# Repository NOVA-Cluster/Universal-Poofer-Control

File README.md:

# Universal Poofer Control — revision A.3

Controller platform intended for creating theatrical flame effects devices (poofers), including stage effects, flame-art installations and custom theatrical projects. The current design remains an engineering preview, not a qualified live-effects system.

Editable KiCad 10 design for ESP32-S3-WROOM-1-N8, eight relay-controlled 12 VDC valves and eight **grounded switches, active LOW**, with nominal **20 mA board-sourced wetting current**. The field circuits are designed for continuous ±100 V relative to shared return, including power-off conditions. Physical fault and temperature qualification remains required.

Open `Universal_Poofer_Control.kicad_pro`. The schematic has **24 numbered A3 sheets**, grouped by function with repeated channel layouts and local wiring. The **200 × 160 mm PCB is placement only**: 0.5 mm footprint-origin grid, no tracks, vias or copper pours. `AGENTS.md` makes these engineering and appearance standards persistent.

**New to the board?** Start with the [Hardware User Guide](docs/hardware-user-guide.md), the maintained customer-facing source of truth for features, project ideas, wiring, first-use commissioning, expansion and schematic navigation. A.3 remains an engineering preview until qualification.

## Files

| Deliverable | Location |
|---|---|
| Customer hardware guide | `docs/hardware-user-guide.md` / `output/pdf/Universal_Poofer_Control_Hardware_User_Guide.pdf` |
| Editable schematic / board | `Universal_Poofer_Control.kicad_sch` / `.kicad_pcb` |
| Schematic PDF | `output/pdf/Universal_Poofer_Control_A3.pdf` |
| Board preview | `output/pcb/placement_top.png` / `.pdf` |
| Full hardware review | `docs/hardware-design-review-A3.md` |
| Analog and stop evidence | `docs/hardware-topology-review.md`, `docs/hardware-stop-logic-review.md` |
| Complete connector reference | `docs/connector-pinouts.md` |
| Arduino / PlatformIO project | `firmware/` |
| Exact JLC assembly BOM / stock | `bom/JLCPCB_BOM.csv`, `bom/assembly_availability.csv` |

## Power and valves

J1: pin 1 regulated **5.0–5.25 V, ≥1 A**, pin 2 GND. J2: pin 1 **12 V, ≥0.5 A**, pin 2 GND, powering analog circuits and eight approximately 30 mA relay coils. Both supplies share logic/input GND. Each expansion module has independent supplies; chain headers have no power pins.

Feed each `J31…J38.1 / COM` from an **individually fused external 12 V valve supply**. Connect its valve between `J41…J48.1 / NO` and `.2 / RETURN`, and connect RETURN to that external supply's negative. Valve RETURN is separate from logic GND. The aggregate valve current does not pass through a common board power header. Plan for **1 A per valve**. The relays' 10 A resistive-contact rating is not the header or inductive-load rating. NC is auxiliary and must not be used for shutdown-controlled valve loads.

All interfaces are 2.54 mm / 100 mil headers. Every resistor/capacitor is **0805**. Ordinary ICs are SOIC; other packages are DPAK, SOT-223, SOT-23 and SMA/SMB. The ESP32 is a replaceable castellated module. There are no 0402/0603 passives or TSSOP logic.

## Switch inputs

Close a dry contact between `J11…J18.1 / FIELD` and `.2 / GND`. LOW means closed; an open contact is inactive. A compensated LM2902 / HV PNP source supplies approximately 20 mA to a grounded contact. A backup limiter bounds saturation-recovery surges. Independent protected paths sense contact state and negative faults.

Closed FIELD must be ≤0.3 V including wiring/contact drop; ≤10 Ω total series-loop contact/return resistance (including every contact and cable in an expansion chain) is a conservative system target. Wetting is nominal, not calibrated or a guaranteed 20 mA minimum. Source accuracy, all-channel settling, MLCC capacitance, cold compliance, fault quench and hot powered-off leakage need prototype tests.

Each module captures 16 bits: active-HIGH fault byte, then active-LOW contact byte. Firmware computes `closed = (~contacts_n) & (~faults)`. Fault detection has a finite threshold: small negative voltages near ground can still read as closed. ±100 V endurance does not imply every intermediate voltage has a unique diagnostic interpretation. This protection applies only to FIELD pins; power, GPIO, I²C, expansion logic and GND retain ordinary limits.

## Hardware emergency stop

J9 connects an external **NC contact** between ESTOP_FIELD and ESTOP_CHAIN_OUT. Opening the loop, disconnecting it, or asserting its field fault removes permission. The master supplies nominal 20 mA. Fit **J10 ground termination only on the last module**; on a single board it is that board. Remove intermediate terminators.

Hardware clears an edge-triggered RUN flip-flop, disables actual 595 `/OE`, and cuts relay-coil power. A 3.3 V supervisor blocks startup/brownout; logic-powered supply monitors also clear RUN on loss of 5 V or raw 12 V (nominal trips about 4.27 V / 8.88 V). Restoring the loop or a supply cannot restart while ARM is held. A fresh arm edge is required. Actual hardware inhibit propagates downstream without firmware cooperation.

GPIO18 reads protected loop permission; GPIO21 reads protected local RUN. Series isolation prevents GPIO backdrive from overriding hardware. GPIO2 observes the physical host jumper through 100 kΩ.

This is a single-channel prototype shutdown circuit. Coil removal cannot open a welded relay contact, and a short across an NC contact can bypass that contact. Use an independent valve-power disconnect where those faults must stop flow. Measure actual relay/valve closure time and clamp energy. No safety certification or shutdown-time rating is established.

## Expansion and I²C

Connect J21 DOWN to the next J20 UP with matching pin numbers. Fit **JP1 on exactly one host**, leave it absent on expanders, and configure roles with power off. Reset after role changes. Do not hot-plug an armed control chain.

| Pin | J20 UP | J21 DOWN |
|---:|---|---|
| 1, 2 | GND | GND |
| 3 | Clock input | Buffered clock |
| 4 | 595 serial input | Local 595 QH′ |
| 5 | Input stream returned upstream | Input stream from next module |
| 6 | Latch input | Buffered latch |
| 7 | Active-low arm/inhibit input | Actual hardware-gated inhibit |
| 8 | Clear input | Buffered clear |
| 9 | Parallel-load input | Buffered parallel load |
| 10 | GND | GND |
| 11 | ESTOP_FIELD | ESTOP_CHAIN_OUT |
| 12, 13, 14 | GND | GND |
| **15** | **I²C SDA common bus** | **I²C SDA common bus** |
| **16** | **I²C SCL common bus** | **I²C SCL common bus** |

LVC244 buffers regenerate shift signals with power-off isolation and 33 Ω series resistors. UP controls have their own safe pulls, so an unplugged expander inhibits. The return tail pulls HIGH, filling absent-module fault bytes with FF. Write 595 bytes farthest-first and read 165 words host-first. Firmware supports a configured **1–32 modules**, each adding 8 output and 16 input bits; this allocation is not a qualified cable-length or physical-chain limit.

I²C uses GPIO8/SDA and GPIO9/SCL on each private MCU B-side bus, isolated onto the common A-side by PCA9517A. Only A sides join together. Fit JP2 at one common pullup provider, normally the host: **2.2 kΩ common**, **4.7 kΩ private** pullups. Start at **100 kHz**, qualify common capacitance ≤400 pF and LOW/high/rise-time/leakage behavior. Thirty-two buffers can consume 224 pF before cables. Unique peripheral addresses and bus loading are independent of shift-chain expansion. [NXP PCA9517A datasheet](https://www.nxp.com/docs/en/data-sheet/PCA9517A.pdf); see `docs/i2c-interface-review.md`.

## GPIO, programming and firmware

| Function | GPIO |
|---|---:|
| Clock / output serial / input serial | 6 / 4 / 5 |
| Latch / MCU inhibit / clear / input load | 7 / 15 / 16 / 17 |
| Loop permission / local RUN / role monitor | 18 / 21 / 2 |
| I²C SDA / SCL | 8 / 9 |
| UART TX / RX | 43 / 44 |
| USB D− / D+ | 19 / 20 |

J3/J4 expose module pins 1–40; pad 41 is grounded on the PCB. GPIO0/3/45/46 are straps. J6 is EN/GND/BOOT; J7 is TX/RX/GND for a 3.3 V UART adapter. Exposed USB signals need a suitable protected external connection. Every header pin, including J5 debug/service access, is listed in `docs/connector-pinouts.md`.

The Arduino/PlatformIO scaffold starts inhibited, clears/latches all configured outputs, requires explicit arm and hardware RUN acknowledgement, and supports bounded 1–1000 ms pulses with a 500 ms renewable control lease. I²C scans are explicit and disarmed-only. It does not automatically map switches to valves. Nothing has been flashed.

From `firmware/`: `pio run -e poofer_uart -e poofer_usb -e poofer_chain32_compile`; `pio test -e native`. `firmware/README.md` documents an isolated build environment. Three target builds and all 24 tests passed; physical timing, interrupts and watchdog remain hardware tests.

## Review, assembly and regeneration

The full review records native ERC, exported-netlist contract checks, saved-board parity, placement DRC, schematic/PCB/cross/thermal/EMC/lifecycle analyzers, generic SPICE and dedicated analog/stop models, with evidence and limitations. The unrouted PCB is not a fabrication release; production Gerbers and final routing/CPL validation have not been produced.

`scripts/build_schematic.py` invokes the A.3 builder; `scripts/build_pcb.py` reproduces placement; `scripts/validate_a3.py` checks the authoritative KiCad-exported netlist. Preserve and reconcile manual or unsaved editor work before regeneration. Local KiCad CLI/pcbnew paths must match the installation. Earlier incompatible active-HIGH / wetting-sink revisions are preserved locally under ignored `archive/`; they are not part of a fresh clone. See [repository contents](docs/repository-content.md) for the versioned sources and local artifacts.

All exact parts had JLC assembly inventory on 2026-10-03; Basic was preferred, with Extended devices retained where electrical/package requirements justify them. Mixed SMT/THT header/relay assembly needs the appropriate service and quote. Recheck stock and orientations at ordering. [JLC assembly capabilities](https://jlcpcb.com/capabilities/pcb-assembly-capabilities). Inventory is not lifecycle evidence: the available LCSC audit returns unknown lifecycle status; production release still needs manufacturer/distributor lifecycle checks.

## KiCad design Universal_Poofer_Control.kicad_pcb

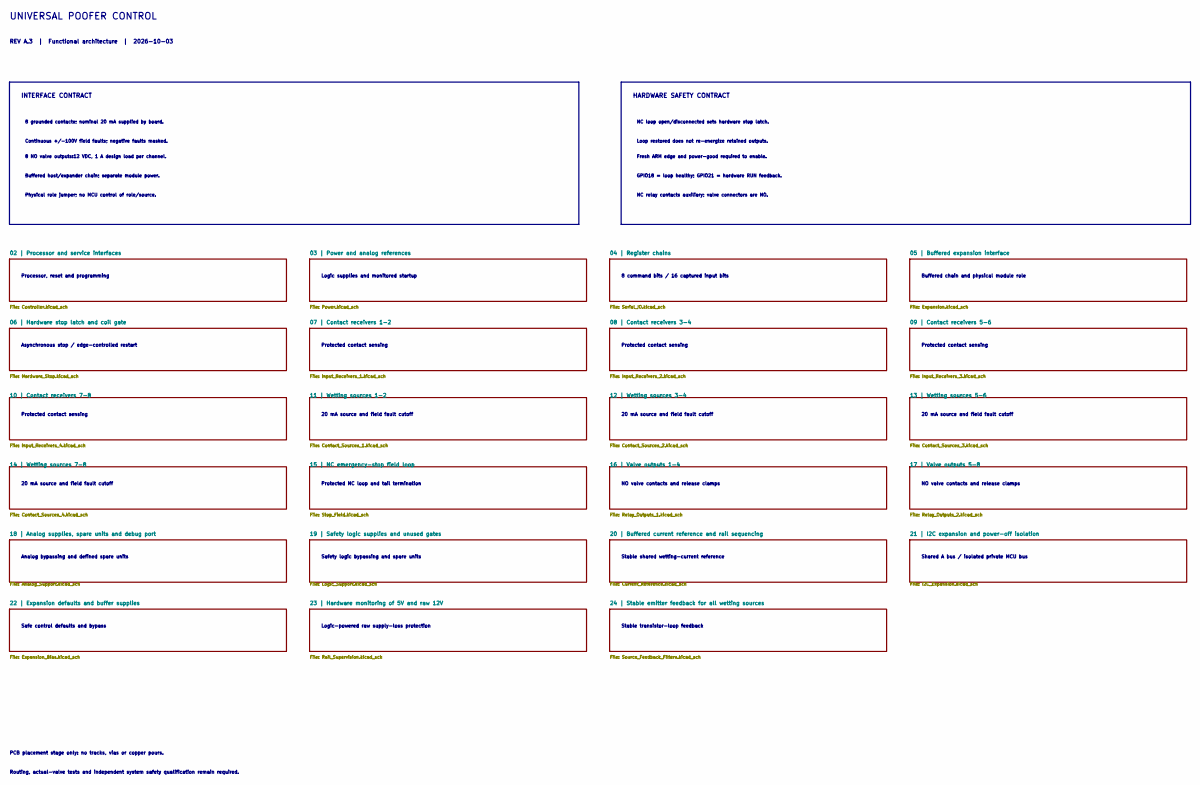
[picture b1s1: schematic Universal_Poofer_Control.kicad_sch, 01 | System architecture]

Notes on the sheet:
UNIVERSAL POOFER CONTROL
REV A.3 | Functional architecture | 2026-10-03
INTERFACE CONTRACT
HARDWARE SAFETY CONTRACT
8 grounded contacts; nominal 20 mA supplied by board.
Continuous +/-100V field faults; negative faults masked.
8 NO valve outputs:12 VDC, 1 A design load per channel.
Buffered host/expander chain; separate module power.
Physical role jumper; no MCU control of role/source.
NC loop open/disconnected sets hardware stop latch.
Loop restored does not re-energize retained outputs.
Fresh ARM edge and power-good required to enable.
GPIO18 = loop healthy; GPIO21 = hardware RUN feedback.
NC relay contacts auxiliary; valve connectors are NO.
Processor, reset and programming
Logic supplies and monitored startup
8 command bits / 16 captured input bits
Buffered chain and physical module role
Asynchronous stop / edge-controlled restart
Protected contact sensing
20 mA source and field fault cutoff
Protected NC loop and tail termination
NO valve contacts and release clamps
Analog bypassing and defined spare units
Safety logic bypassing and spare units
Stable shared wetting-current reference
Shared A bus / isolated private MCU bus
Safe control defaults and bypass
Logic-powered raw supply-loss protection
Stable transistor-loop feedback
PCB placement stage only: no tracks, vias or copper pours.
Routing, actual-valve tests and independent system safety qualification remain required.

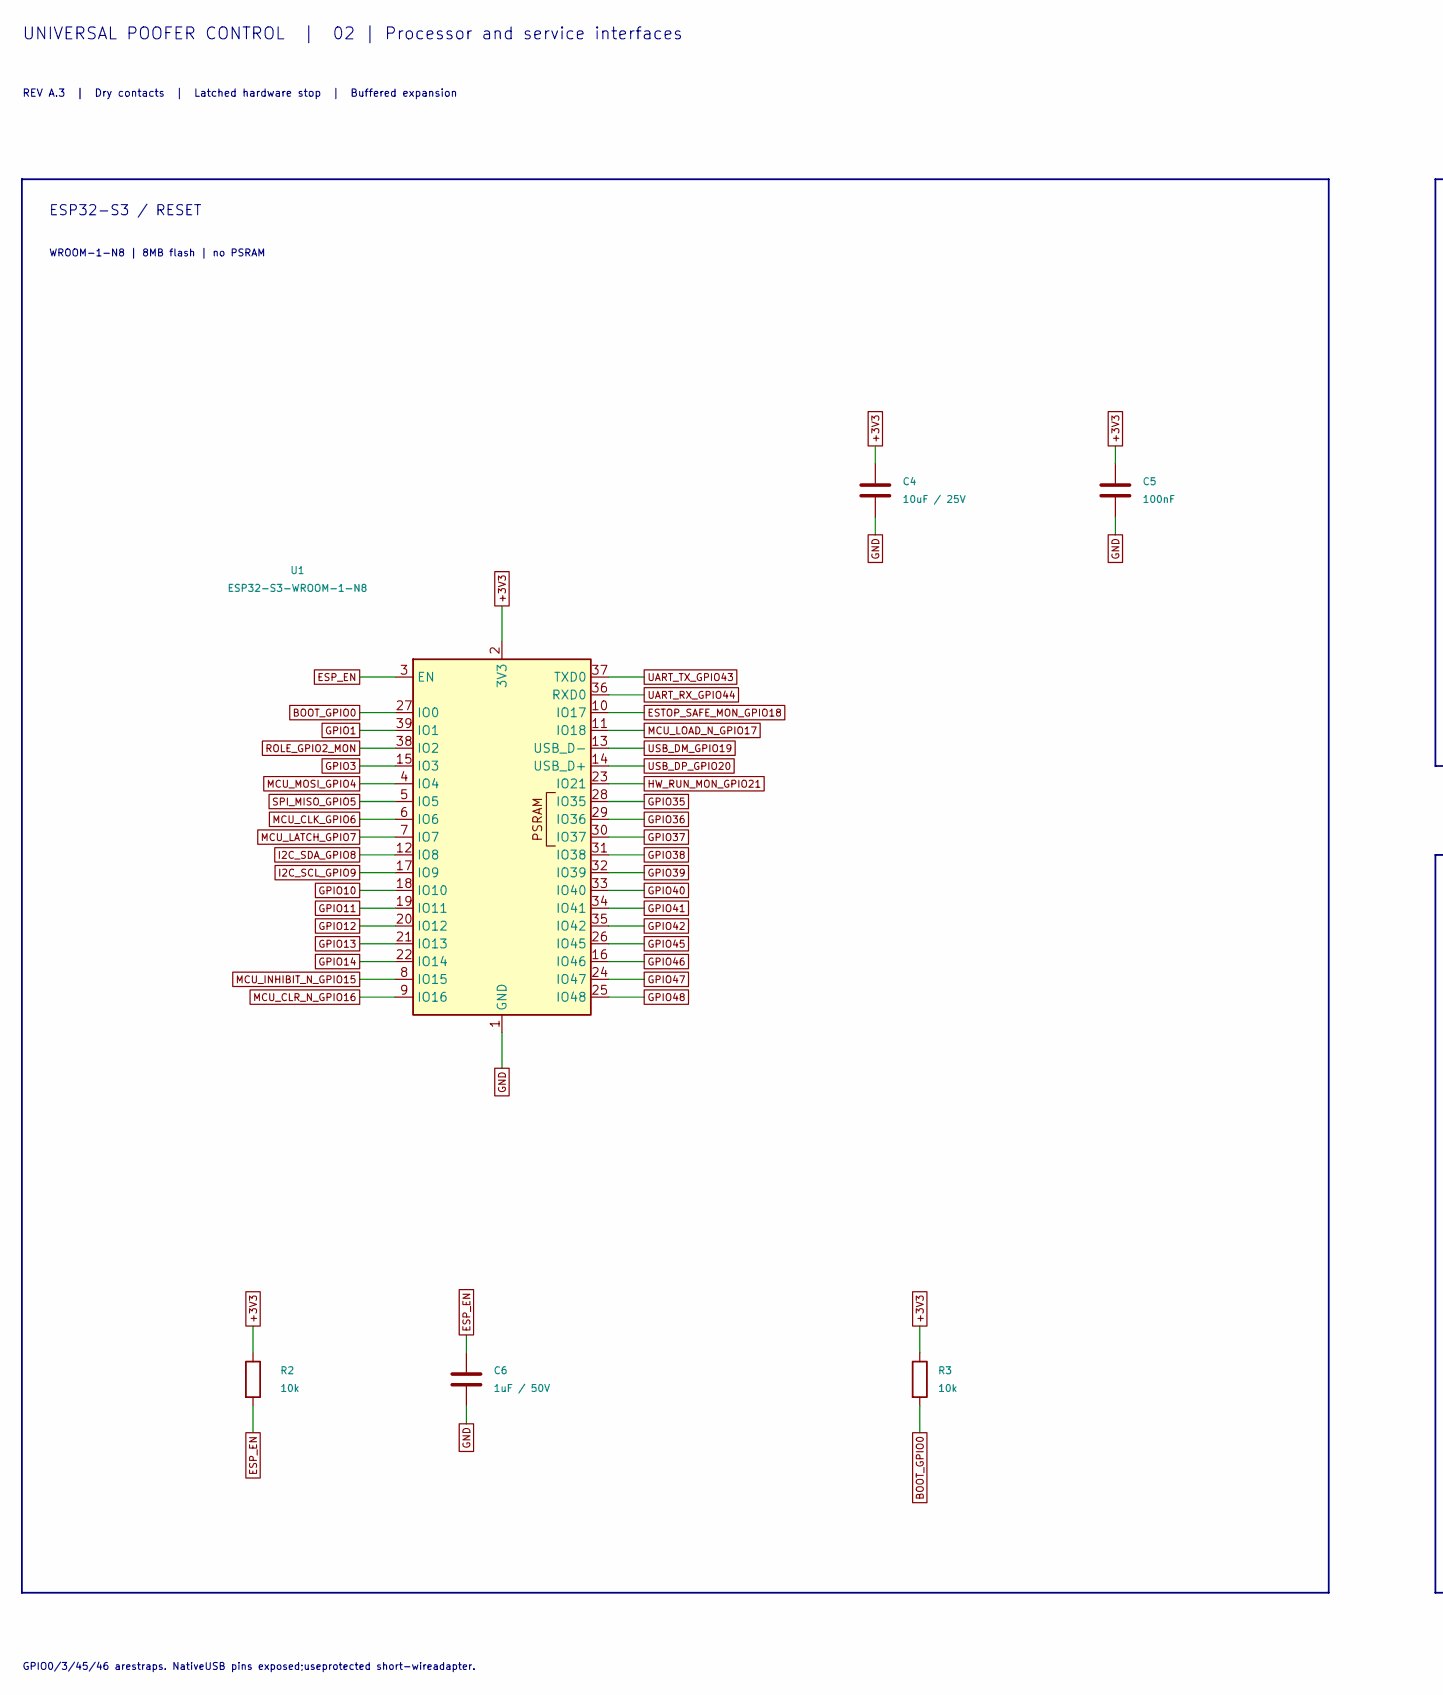
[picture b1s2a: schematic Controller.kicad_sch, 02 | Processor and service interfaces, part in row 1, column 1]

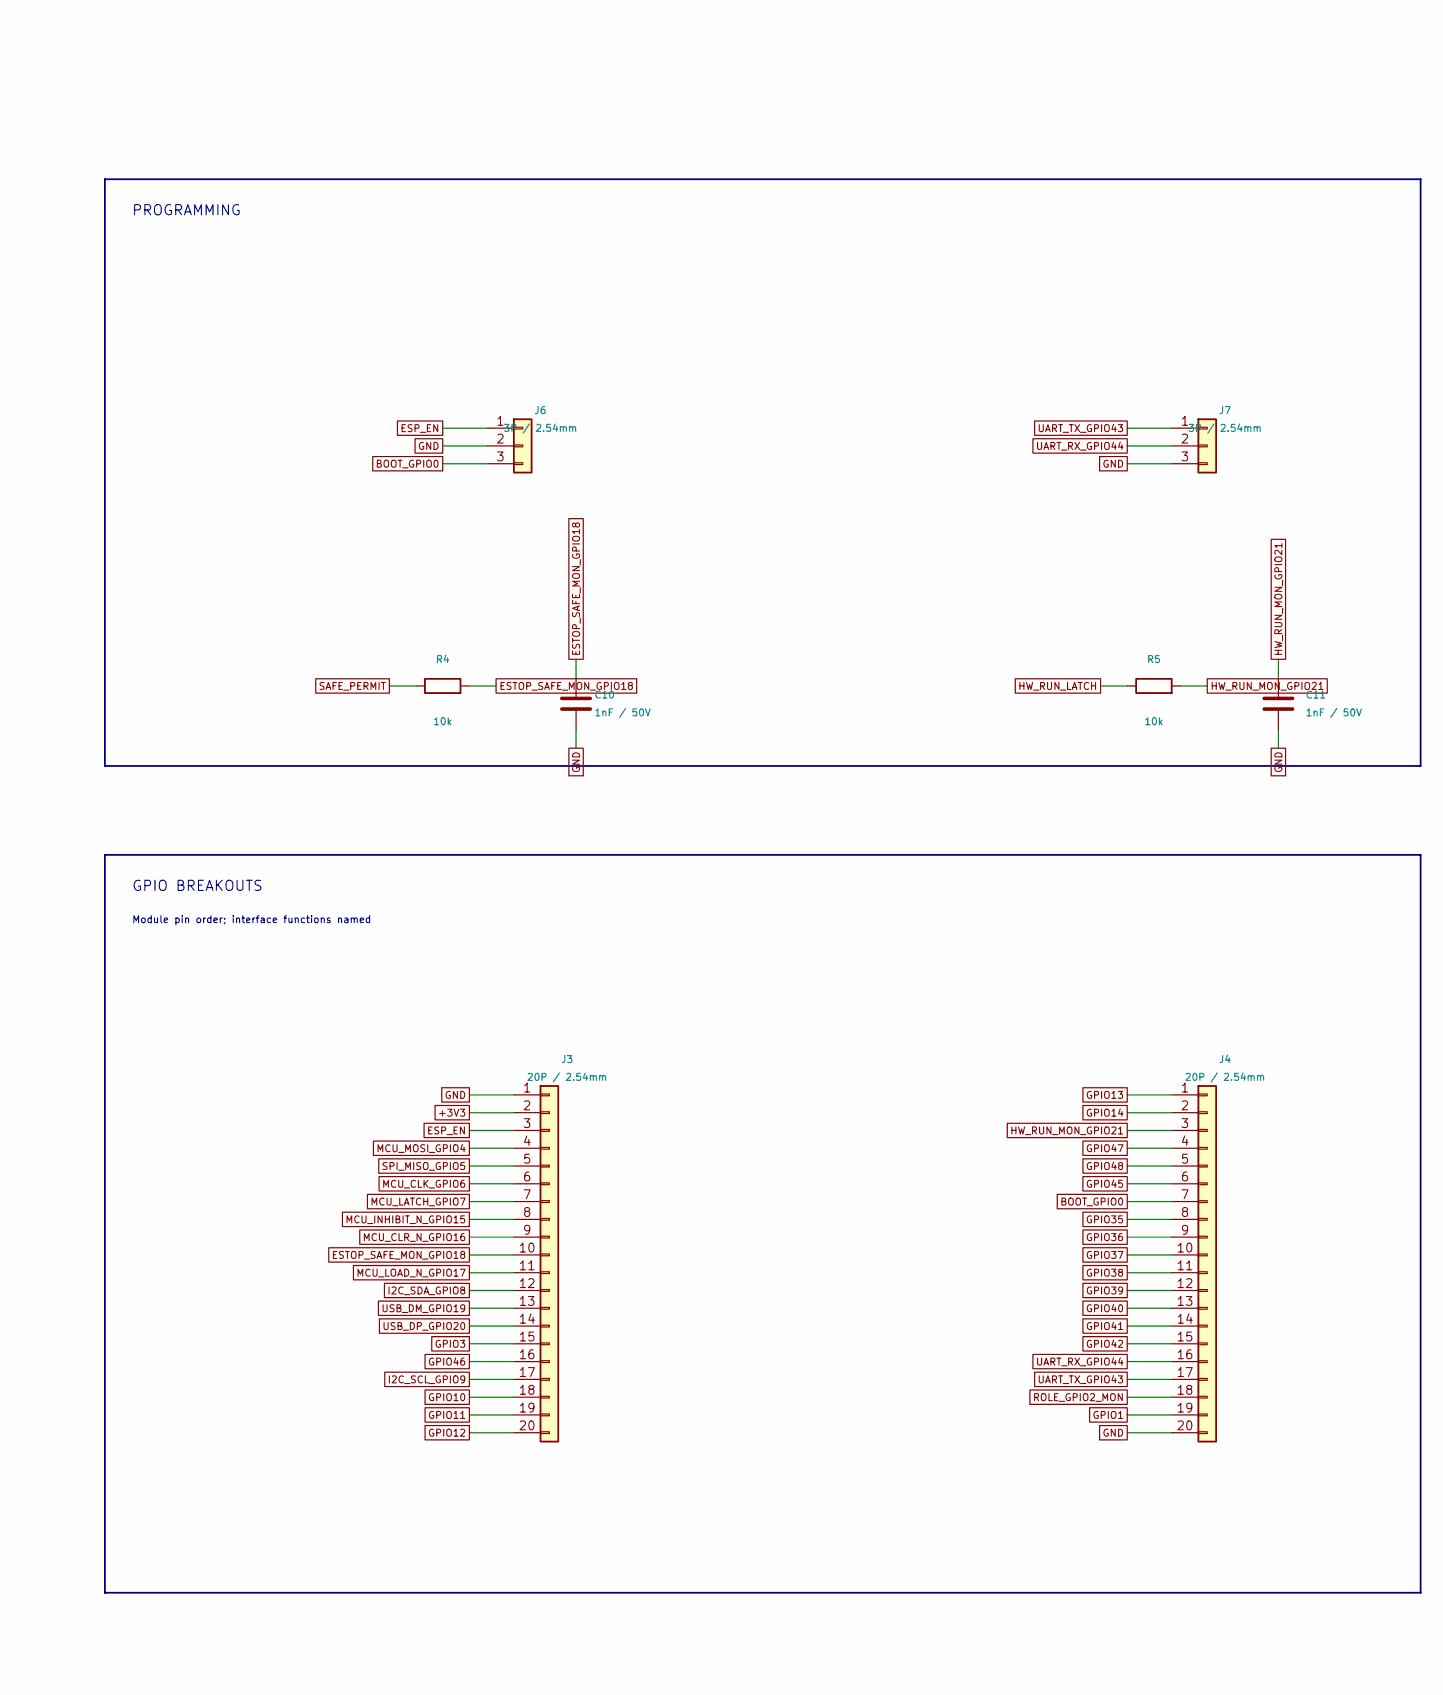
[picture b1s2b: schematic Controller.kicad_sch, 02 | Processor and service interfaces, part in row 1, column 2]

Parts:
C4: 10uF / 25V; C_0805_2012Metric; MPN CL21A106KAYNNNE; LCSC C15850
C5: 100nF; C_0805_2012Metric; MPN CC0805KRX7R9BB104; LCSC C49678
C6: 1uF / 50V; C_0805_2012Metric; MPN CL21B105KBFNNNE; LCSC C28323
C10, C11: 1nF / 50V; C_0805_2012Metric; MPN CL21B102KBANNNC; LCSC C51210
J3, J4: 20P / 2.54mm; PinHeader_1x20_P2.54mm_Vertical; MPN 2.54-1*20P; LCSC C50981
J6, J7: 3P / 2.54mm; PinHeader_1x03_P2.54mm_Vertical; MPN B-2100S03P-A110; LCSC C124376
R2, R3, R4, R5: 10k; R_0805_2012Metric; MPN 0805W8F1002T5E; LCSC C17414
U1: ESP32-S3-WROOM-1-N8; ESP32-S3-WROOM-1; MPN ESP32-S3-WROOM-1-N8; LCSC C2913198

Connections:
+3V3: C4.1, C5.1, J3.2, R2.1, R3.1, U1.2 (3V3); also elsewhere on the board
BOOT_GPIO0: J4.7, J6.3, R3.2, U1.27 (IO0)
ESP_EN: C6.1, J3.3, J6.1, R2.2, U1.3 (EN)
ESTOP_SAFE_MON_GPIO18: C10.1, J3.10, R4.2, U1.10 (IO17); also elsewhere on the board
GND: C4.2, C5.2, C6.2, C10.2, C11.2, J3.1, J4.20, J6.2, J7.3, U1.1 (GND), U1.40 (GND), U1.41 (GND); also elsewhere on the board
GPIO1: J4.19, U1.39 (IO1)
GPIO3: J3.15, U1.15 (IO3)
GPIO10: J3.18, U1.18 (IO10)
GPIO11: J3.19, U1.19 (IO11)
GPIO12: J3.20, U1.20 (IO12)
GPIO13: J4.1, U1.21 (IO13)
GPIO14: J4.2, U1.22 (IO14)
GPIO35: J4.8, U1.28 (IO35)
GPIO36: J4.9, U1.29 (IO36)
GPIO37: J4.10, U1.30 (IO37)
GPIO38: J4.11, U1.31 (IO38)
GPIO39: J4.12, U1.32 (IO39)
GPIO40: J4.13, U1.33 (IO40)
GPIO41: J4.14, U1.34 (IO41)
GPIO42: J4.15, U1.35 (IO42)
GPIO45: J4.6, U1.26 (IO45)
GPIO46: J3.16, U1.16 (IO46)
GPIO47: J4.4, U1.24 (IO47)
GPIO48: J4.5, U1.25 (IO48)
HW_RUN_LATCH: R5.1; also elsewhere on the board
HW_RUN_MON_GPIO21: C11.1, J4.3, R5.2, U1.23 (IO21); also elsewhere on the board
I2C_SCL_GPIO9: J3.17, U1.17 (IO9); also elsewhere on the board
I2C_SDA_GPIO8: J3.12, U1.12 (IO8); also elsewhere on the board
MCU_CLK_GPIO6: J3.6, U1.6 (IO6); also elsewhere on the board
MCU_CLR_N_GPIO16: J3.9, U1.9 (IO16); also elsewhere on the board
MCU_INHIBIT_N_GPIO15: J3.8, U1.8 (IO15); also elsewhere on the board
MCU_LATCH_GPIO7: J3.7, U1.7 (IO7); also elsewhere on the board
MCU_LOAD_N_GPIO17: J3.11, U1.11 (IO18); also elsewhere on the board
MCU_MOSI_GPIO4: J3.4, U1.4 (IO4); also elsewhere on the board
ROLE_GPIO2_MON: J4.18, U1.38 (IO2); also elsewhere on the board
SAFE_PERMIT: R4.1; also elsewhere on the board
SPI_MISO_GPIO5: J3.5, U1.5 (IO5); also elsewhere on the board
UART_RX_GPIO44: J4.16, J7.2, U1.36 (RXD0)
UART_TX_GPIO43: J4.17, J7.1, U1.37 (TXD0)
USB_DM_GPIO19: J3.13, U1.13 (USB_D-)
USB_DP_GPIO20: J3.14, U1.14 (USB_D+)

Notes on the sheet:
UNIVERSAL POOFER CONTROL | 02 | Processor and service interfaces
REV A.3 | Dry contacts | Latched hardware stop | Buffered expansion
ESP32-S3 / RESET
WROOM-1-N8 | 8MB flash | no PSRAM
PROGRAMMING
GPIO BREAKOUTS
Module pin order; interface functions named
GPIO0/3/45/46 arestraps. NativeUSB pins exposed;useprotected short-wireadapter.

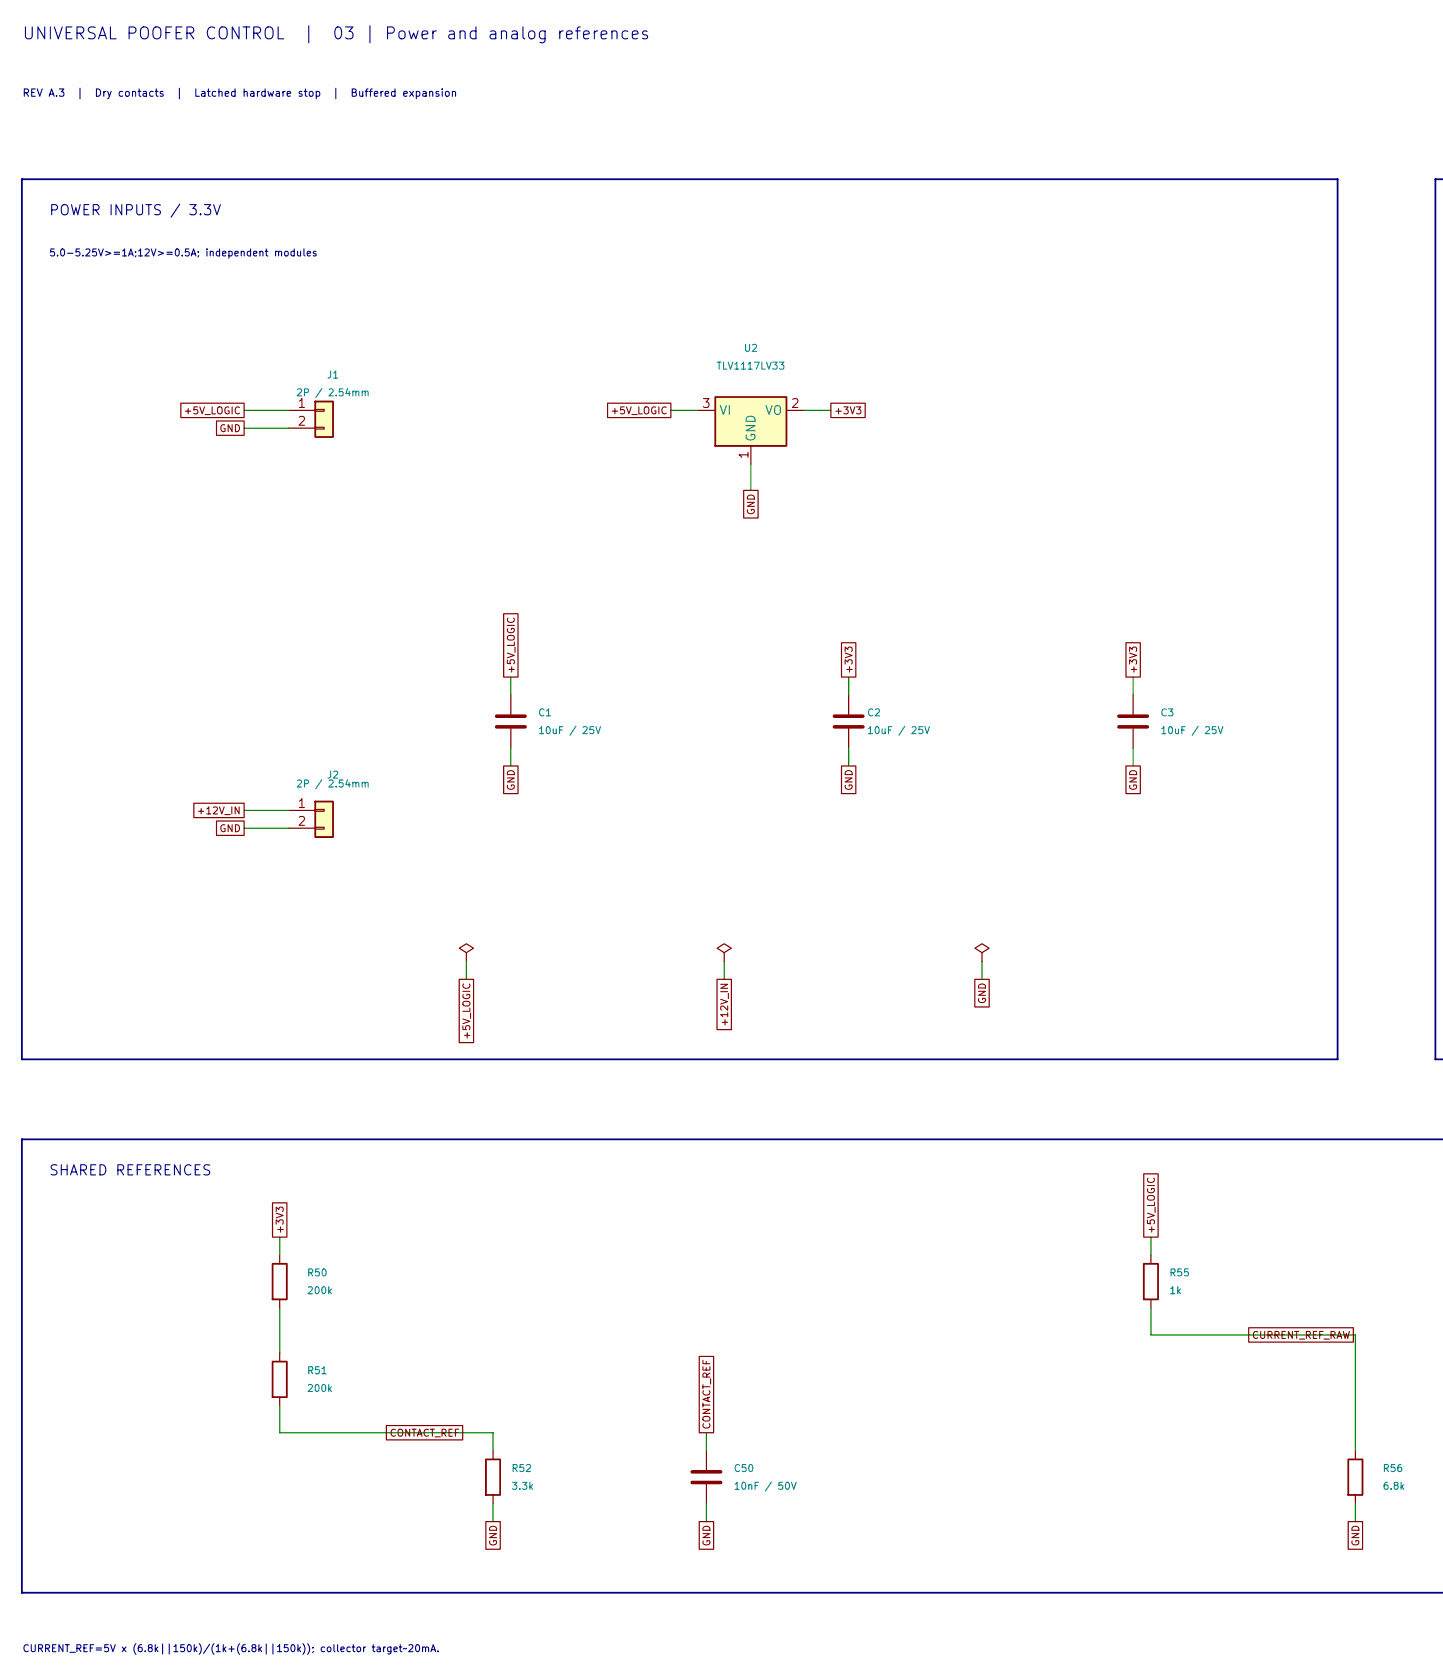
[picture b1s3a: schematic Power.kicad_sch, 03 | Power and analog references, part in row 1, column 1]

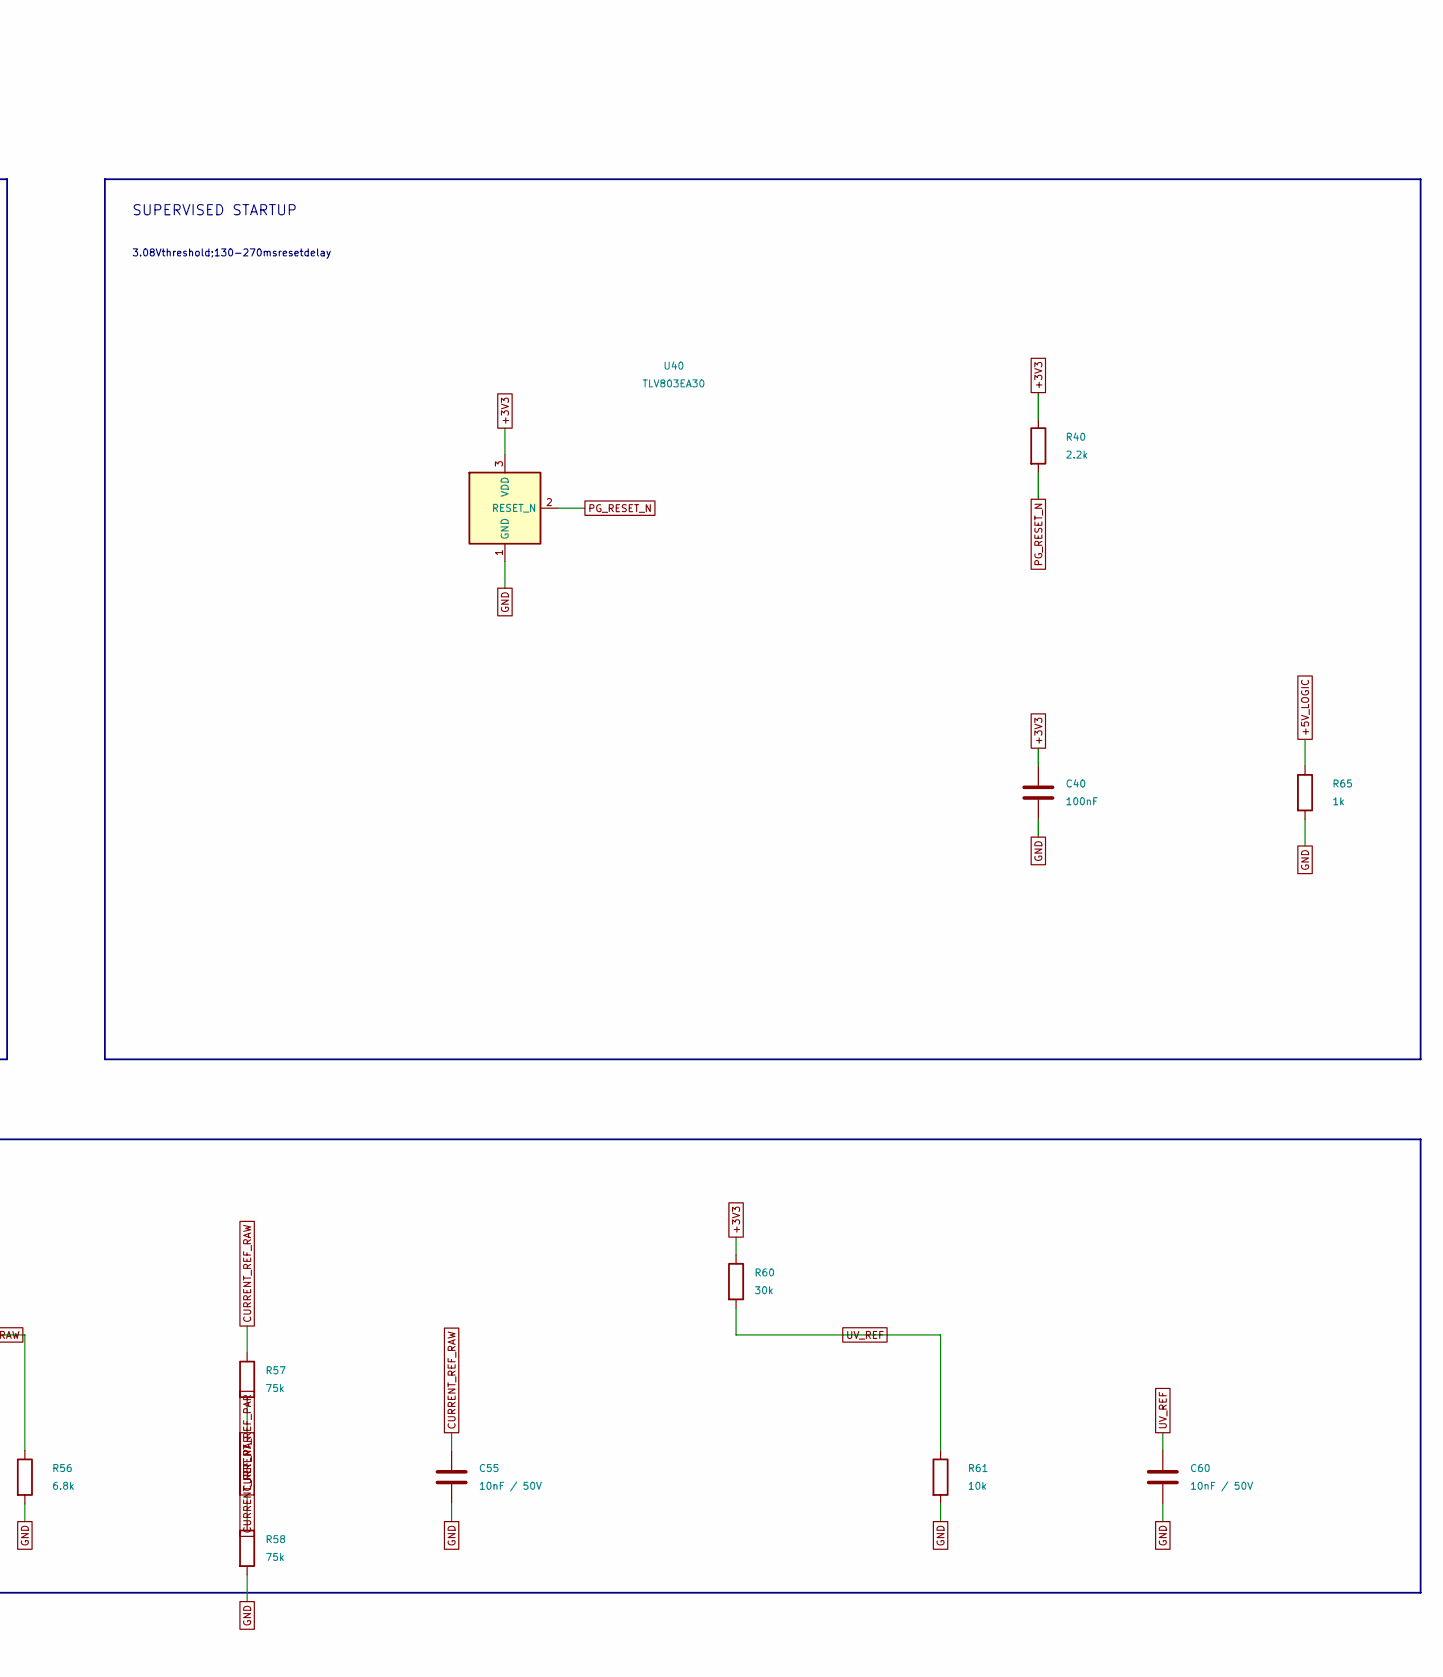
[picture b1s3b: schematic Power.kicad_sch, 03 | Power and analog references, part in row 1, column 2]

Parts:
C1, C2, C3: 10uF / 25V; C_0805_2012Metric; MPN CL21A106KAYNNNE; LCSC C15850
C40: 100nF; C_0805_2012Metric; MPN CC0805KRX7R9BB104; LCSC C49678
C50, C55, C60: 10nF / 50V; C_0805_2012Metric; MPN CL21B103KBANNNC; LCSC C1710
J1, J2: 2P / 2.54mm; PinHeader_1x02_P2.54mm_Vertical; MPN B-2100S02P-A110; LCSC C124375
R40: 2.2k; R_0805_2012Metric; MPN 0805W8F2201T5E; LCSC C17520
R50, R51: 200k; R_0805_2012Metric; MPN 0805W8F2003T5E; LCSC C17539
R52: 3.3k; R_0805_2012Metric; MPN 0805W8F3301T5E; LCSC C26010
R55, R65: 1k; R_0805_2012Metric; MPN 0805W8F1001T5E; LCSC C17513
R56: 6.8k; R_0805_2012Metric; MPN 0805W8F6801T5E; LCSC C17772
R57, R58: 75k; R_0805_2012Metric; MPN 0805W8F7502T5E; LCSC C17819
R60: 30k; R_0805_2012Metric; MPN 0805W8F3002T5E; LCSC C17621
R61: 10k; R_0805_2012Metric; MPN 0805W8F1002T5E; LCSC C17414
U2: TLV1117LV33; SOT-223-3_TabPin2; MPN TLV1117LV33DCYR; LCSC C15578
U40: TLV803EA30; SOT-23; MPN TLV803EA30DBZR; LCSC C5218924

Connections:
+3V3: C2.1, C3.1, C40.1, R40.1, R50.1, R60.1, U2.2 (VO), U40.3 (VDD); also elsewhere on the board
+5V_LOGIC: C1.1, J1.1, R55.1, R65.1, U2.3 (VI); also elsewhere on the board
+12V_IN: J2.1; also elsewhere on the board
CONTACT_REF: C50.1, R51.2, R52.1; also elsewhere on the board
CURRENT_REF_PAR: R57.2, R58.1
CURRENT_REF_RAW: C55.1, R55.2, R56.1, R57.1; also elsewhere on the board
GND: C1.2, C2.2, C3.2, C40.2, C50.2, C55.2, C60.2, J1.2, J2.2, R52.2, R56.2, R58.2, R61.2, R65.2, U2.1 (GND), U40.1 (GND); also elsewhere on the board
unnamed: R50.2, R51.1
PG_RESET_N: R40.2, U40.2 (RESET_N); also elsewhere on the board
UV_REF: C60.1, R60.2, R61.1; also elsewhere on the board

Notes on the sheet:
UNIVERSAL POOFER CONTROL | 03 | Power and analog references
REV A.3 | Dry contacts | Latched hardware stop | Buffered expansion
POWER INPUTS / 3.3V
5.0-5.25V>=1A;12V>=0.5A; independent modules
SUPERVISED STARTUP
3.08Vthreshold;130-270msresetdelay
SHARED REFERENCES
CURRENT_REF=5V x (6.8k||150k)/(1k+(6.8k||150k)); collector target~20mA.

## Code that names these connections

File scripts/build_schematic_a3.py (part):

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for u in find_all(get_symbol('RF_Module:ESP32-S3-WROOM-1'),'symbol'):
 for p in find_all(u,'pin'):
  n=find_first(p,'number')[1];name=find_first(p,'name')[1]
  if n not in gpio:gpio[n]='GND' if name=='GND' else {'USB_D-':'USB_DM_GPIO19','USB_D+':'USB_DP_GPIO20'}.get(name,name.replace('IO','GPIO'))
m=P(ctrl,'RF_Module:ESP32-S3-WROOM-1','U1','C2913198',83.82,132.08,footprint='RF_Module:ESP32-S3-WROOM-1',notes='GPIO2rolemonitoronly;18SAFE;21RUN. Antenna keepout mandatory.');seen=set()
for n,v in gpio.items():
 if m[n][:2] not in seen:N(ctrl,m,n,v,5.08);seen.add(m[n][:2])
ctrl.header('J3',280.67,191.77,[gpio[str(i)] for i in range(1,21)]);ctrl.header('J4',374.65,191.77,[gpio[str(i)] for i in range(21,41)])
ctrl.header('J6',276.86,76.2,['ESP_EN','GND','BOOT_GPIO0'],'Reset1-2;BOOT3-2 heldduringresetforROMdownload.');ctrl.header('J7',374.65,76.2,['UART_TX_GPIO43','UART_RX_GPIO44','GND'],'3.3VUART,self-poweredboard.')
C(ctrl,'C4',137,83,'+3V3','GND','10uF / 25V','C15850','Capacitor_SMD:C_0805_2012Metric');C(ctrl,'C5',172,83,'+3V3','GND');R(ctrl,'R2','C17414',48,210,'+3V3','ESP_EN','10k');C(ctrl,'C6',79,210,'ESP_EN','GND','1uF / 50V','C15849');R(ctrl,'R3','C17414',143,210,'+3V3','BOOT_GPIO0','10k')
R(ctrl,'R4','C17414',266,111,'SAFE_PERMIT','ESTOP_SAFE_MON_GPIO18','10k',90,note='MCU/header cannot back-drivehardware safety permission.')
R(ctrl,'R5','C17414',367,111,'HW_RUN_LATCH','HW_RUN_MON_GPIO21','10k',90,note='MCU/header cannot back-drivehardware stop latch.')
C(ctrl,'C10',284,113,'ESTOP_SAFE_MON_GPIO18','GND','1nF / 50V','C1588');C(ctrl,'C11',385,113,'HW_RUN_MON_GPIO21','GND','1nF / 50V','C1588')
ctrl.text('GPIO0/3/45/46 arestraps. NativeUSB pins exposed;useprotected short-wireadapter.',15,250,1.0)

pw.block('POWER INPUTS / 3.3V',15,38,188,126,'5.0-5.25V>=1A;12V>=0.5A; independent modules');pw.block('SUPERVISED STARTUP',217,38,188,126,'3.08Vthreshold;130-270msresetdelay');pw.block('SHARED REFERENCES',15,175,390,65)
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 for n,v in [(16,'+3V3'),(8,'GND'),(1,'BUS_LOAD_N'),(2,'BUS_CLK'),(15,'GND')]:N(sr,p,n,v)
 sr.nc(p,7)
for n,ch in [(11,1),(12,2),(13,3),(14,4),(3,5),(4,6),(5,7),(6,8)]:N(sr,a,n,f'IN{ch}_N');N(sr,b,n,f'IN{ch}_FAULT')
N(sr,a,10,'NEXT_SERIAL_IN');N(sr,b,9,'SPI_MISO_GPIO5');sr.wire(a['9'][:2],(310,a['9'][1]));sr.wire((310,a['9'][1]),(310,b['10'][1]));sr.wire((310,b['10'][1]),b['10'][:2])
for ref,x,y in [('C7',42,203),('C8',239,215),('C9',394,215)]:C(sr,ref,x,y,'+3V3','GND')
sr.text('SampleQ7beforeclock. TailpulledHIGH fillsabsentmoduleswithFAULTFF,notfalseclosures.',15,252,1.0)

ex.block('PHYSICAL MASTER / EXPANDER ROLE',15,38,390,41,'GPIO2 monitors through100k; cannot override hardware jumper')
ex.header('JP1',65,64,['LOCAL_MASTER_N','GND'],'Closed=master;open=expander. Exactlyonehost.')
R(ex,'R70','C17414',116,62,'+3V3','LOCAL_MASTER_N','10k');R(ex,'R71','C25803',191,62,'LOCAL_MASTER_N','ROLE_GPIO2_MON','100k',90)
ex.block('UP / DOWN PORTS',15,89,121,153,'2x8male,2.54mm; independentmodulepower');ex.block('ISOLATED LOCAL / UP DRIVERS',145,89,260,83);ex.block('REGENERATED CHAIN OUTPUTS',145,182,260,60)
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for ref,x,y,nets in [('J20',56,138,up),('J21',113,202,down)]:
 p=P(ex,'Connector_Generic:Conn_02x08_Odd_Even',ref,'C68234',x,y,value='EXP_UP' if ref=='J20' else 'EXP_DOWN',footprint='Connector_PinHeader_2.54mm:PinHeader_2x08_P2.54mm_Vertical',notes='NOPOWERPINS;independentlocalsupplies. Pin11NCcontinuity,terminateonlylast.')
 for n,v in enumerate(nets,1):N(ex,p,n,v)
mp=[(2,18),(4,16),(6,14),(8,12),(17,3),(15,5),(13,7),(11,9)];dst=['BUS_CLK','BUS_SER_IN','BUS_LATCH','BUS_LOAD_N','BUS_CLR_N','BUS_ARM_N',None,None]
li=['MCU_CLK_GPIO6','MCU_MOSI_GPIO4','MCU_LATCH_GPIO7','MCU_LOAD_N_GPIO17','MCU_CLR_N_GPIO16','MCU_INHIBIT_N_GPIO15','GND','GND'];ri=['UP_CLK','UP_SER','UP_LATCH','UP_LOAD_N','UP_CLR_N','UP_ARM_N','GND','GND'];BN='LVC244A3.3V,Ioff,5Vtolerantinputs;unusedinputsGND.'
for ref,x,inputs,en in [('U50',206,li,'LOCAL_MASTER_N'),('U51',330,ri,'ROLE_RX_OE_N')]:
 p=IC(ex,'74xx:74HC244',ref,'C507250',x,135,note=BN,fp='Package_SO:SOIC-20W_7.5x12.8mm_P1.27mm',val='SN74LVC244A')
 for n,v in [(1,en),(19,en),(10,'GND'),(20,'+3V3')]:N(ex,p,n,v)
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  else:ex.nc(p,o)
p=IC(ex,'74xx:74HC244','U52','C507250',264,211,note=BN,fp='Package_SO:SOIC-20W_7.5x12.8mm_P1.27mm',val='SN74LVC244A')
for n,v in [(1,'GND'),(19,'GND'),(10,'GND'),(20,'+3V3')]:N(ex,p,n,v)
for k,((i,o),a,b) in enumerate(zip(mp,['BUS_CLK','LOCAL_SER_OUT','BUS_LATCH','BUS_LOAD_N','BUS_CLR_N','RLY_OE_ACTUAL_N','SPI_MISO_GPIO5','DOWN_RETURN'],['DOWN_CLK','DOWN_SER','DOWN_LATCH','DOWN_LOAD_N','DOWN_CLR_N','DOWN_ARM_N','UP_RETURN','NEXT_SERIAL_IN'])):
 N(ex,p,i,a)
 if b:N(ex,p,o,f'CHAIN_TX_{k}');R(ex,f'R{80+k}','C23140',375,192+k*6.35,f'CHAIN_TX_{k}',b,'33R',90)
 else:ex.nc(p,o)
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 for k,xx in enumerate([72,99,126]):
  p=R(s,f'R{rb+14+k}','C25803',xx+x,64,val='100k',ang=90);s.wire(prev,p['1'][:2]);prev=p['2'][:2]
 ref='U10' if ch<=4 else 'U11' if ch<=8 else 'U12';u=(ch-1)%4+1;p=IC(s,'Comparator:LM339',ref,'C22427890',175+x,66.54,u,CN,val='LM2901BIDR');mi,pl,ou=cp[u-1]
 s.wire(prev,p[str(pl)][:2]);s.label(SNS,139+x,64,180);N(s,p,mi,'CONTACT_REF');N(s,p,ou,dig)
 sh=R(s,f'R{rb+17}','C23212',139+x,94,b='GND',val='6.8k');s.wire(sh['1'][:2],(sh['1'][0],snap(64)))
 cap=P(s,'Device:C',f'C{100+ch}','C1710',154+x,94,value='10nF / 50V',footprint='Capacitor_SMD:C_0805_2012Metric');N(s,cap,2,'GND');s.wire(cap['1'][:2],(cap['1'][0],snap(64)))
 f1=R(s,f'R{rb+18}','C22935',60+x,115,val='1M',ang=90);f2=R(s,f'R{rb+19}','C22935',106+x,115,val='1M',ang=90)
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N(refpage,v,5,'CURRENT_REF_RAW');refpage.wire(v['7'][:2],(203,90));refpage.wire((203,90),(203,111));refpage.wire((203,111),(159,111));refpage.wire((159,111),(159,v['6'][1]));refpage.wire((159,v['6'][1]),v['6'][:2])
a=R(refpage,'R66','C22775',245,90,val='100R',ang=90,note='Capacitive-load isolation and power-off discharge current limit.')
b=R(refpage,'R67','C22775',283,90,val='100R',ang=90)
refpage.wire(v['7'][:2],a['1'][:2]);refpage.wire(a['2'][:2],b['1'][:2]);refpage.label('CURRENT_REF_DRIVE',214,90,180)
c=P(refpage,'Device:C','C66','C15850',325,111,value='10uF / 25V',footprint='Capacitor_SMD:C_0805_2012Metric',notes='Holds reference during compensation-cap rail transitions; qualify effective capacitance.')
refpage.wire(b['2'][:2],(c['1'][0],b['2'][1]));refpage.wire((c['1'][0],b['2'][1]),c['1'][:2]);refpage.label('CURRENT_REF',307,90,180);N(refpage,c,2,'GND')
refpage.text('200ohm total bounds initial10uF discharge near22mA. Output behavior whenunpowered requireshardwarequalification.',20,174,1.05)
refpage.text('Per-source10k/100nF compensation uses a private negative-input node; never attach it directly to the rawdivider.',20,181,1.05)
refpage.text('Backup PNP limiters bound saturation recovery current. Power-good holds coiloutputs off through settling.',20,188,1.05)
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i2c=new('I2C_Expansion',f'{len(sheets)+1:02d} | I2C expansion and power-off isolation','daisy_chain')
i2c.block('COMMON A BUS / PRIVATE B BUS',15,38,390,118,'AllA sides may share the bus; B sides must remain private')
q=IC(i2c,'Poofer:PCA9517AD','U54','C2802638',205,90,fp='Package_SO:SOIC-8_3.9x4.9mm_P1.27mm',val='PCA9517AD',note='NXP A variant;A sides commonUP/DOWN, B privateMCU. Partial-power isolation.')
for n,nm in [(1,'+3V3'),(8,'+3V3'),(4,'GND'),(5,'PG_RESET_N'),(2,'I2C_SCL_BUS'),(3,'I2C_SDA_BUS'),(7,'I2C_SCL_GPIO9'),(6,'I2C_SDA_GPIO8')]:N(i2c,q,n,nm)
i2c.header('JP2',76,198,['+3V3','I2C_PULLUP_RAIL'],'Close only one common-A pullup pair, normally master. No shared power pins.')
R(i2c,'R120','C4190',124,196,'I2C_PULLUP_RAIL','I2C_SDA_BUS','2.2k');R(i2c,'R121','C4190',174,196,'I2C_PULLUP_RAIL','I2C_SCL_BUS','2.2k')
R(i2c,'R122','C23162',296,196,'+3V3','I2C_SDA_GPIO8','4.7k');R(i2c,'R123','C23162',352,196,'+3V3','I2C_SCL_GPIO9','4.7k')
C(i2c,'C74',136,125,'+3V3','GND');C(i2c,'C75',272,125,'+3V3','GND')
i2c.text('Pins15SDA,16SCL on both chain ports. Default 100 kHz; qualify totalcommon-A capacitance<=400pF.',15,236,1.05)
i2c.text('32 A ports can contribute224pF before cabling.2.2k commonpullups meet the conservativeleakage/high-levelbudget.',15,243,1.05)
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
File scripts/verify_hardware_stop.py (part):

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        out.check(f"relay-coil:{channel}", p(f"K{channel}", 5) == p("Q40", 3), design.pins[f"K{channel}"])
    direct_coil_headers = [(ref, pin) for ref, pin in design.nodes[p("Q40", 3)] if ref.startswith("J")]
    out.check("no-direct-coil-supply-header", not direct_coil_headers, direct_coil_headers)
    out.check("debug-OE-observation-isolated", design.resistor_between("R136", "RLY_OE_ACTUAL_N", "OE_MONITOR_N") and p("J5", 9) == "OE_MONITOR_N", design.pins["R136"])
    out.check("debug-OE-counterdrive-current", design.resistor("R136") >= 100000, {"max_uA": 1e6 * 3.3 * 1.03 / (design.resistor("R136") * .99)})
    hard_oe_headers = [(ref, pin) for ref, pin in design.nodes["RLY_OE_ACTUAL_N"] if ref.startswith("J")]
    out.check("no-direct-hard-OE-header", not hard_oe_headers, hard_oe_headers)

    # Physical role and isolated monitor nodes, including ordinary GPIO counterdrive.
    out.pin(design, "JP1", 1, "LOCAL_MASTER_N")
    out.pin(design, "JP1", 2, "GND")
    for ref, source, target, module_pin in [("R4", "SAFE_PERMIT", "ESTOP_SAFE_MON_GPIO18", 10),
                                           ("R5", "HW_RUN_LATCH", "HW_RUN_MON_GPIO21", 23),
                                           ("R71", "LOCAL_MASTER_N", "ROLE_GPIO2_MON", 38)]:
        out.check(f"isolated-monitor:{ref}", design.resistor_between(ref, source, target) and p("U1", module_pin) == target,
                  {"resistor": design.pins[ref], "module_pin": module_pin, "ohms": design.resistor(ref)})
    for ref, oe in [("U50", "LOCAL_MASTER_N"), ("U51", "ROLE_RX_OE_N"), ("U52", "GND")]:
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        out.check(f"role-selector:{int(role_n)}{int(local_arm)}{int(upstream_arm)}",
                  local_enabled != receiver_enabled and selected == (upstream_arm if role_n else local_arm),
                  {"local_enabled": local_enabled, "receiver_enabled": receiver_enabled, "selected_arm_n": selected})
    out.pin(design, "U50", 15, "MCU_INHIBIT_N_GPIO15")
    out.pin(design, "U50", 5, "BUS_ARM_N")
    out.pin(design, "U51", 15, "UP_ARM_N")
    out.pin(design, "U51", 5, "BUS_ARM_N")
    out.pin(design, "U52", 15, "RLY_OE_ACTUAL_N")
    out.check("forward-actual-inhibit", design.resistor_between("R85", p("U52", 5), "DOWN_ARM_N") and p("J21", 7) == "DOWN_ARM_N",
              {"buffer": design.pins["U52"], "series": design.pins["R85"], "header_pin": p("J21", 7)})
    for net, rail in [("UP_ARM_N", "+3V3"), ("UP_LOAD_N", "+3V3"), ("UP_CLK", "GND"),
                      ("UP_LATCH", "GND"), ("UP_CLR_N", "GND"), ("UP_SER", "GND")]:
        out.check(f"unplugged-default:{net}", bool(design.pull(net, rail)), {"rail": rail, "resistors": design.pull(net, rail)})
    for net, rail in [("MCU_INHIBIT_N_GPIO15", "+3V3"), ("MCU_LOAD_N_GPIO17", "+3V3"),
                      ("MCU_CLK_GPIO6", "GND"), ("MCU_LATCH_GPIO7", "GND"),
                      ("MCU_CLR_N_GPIO16", "GND"), ("MCU_MOSI_GPIO4", "GND")]:
        out.check(f"MCU-high-Z-default:{net}", bool(design.pull(net, rail)), {"rail": rail, "resistors": design.pull(net, rail)})
    out.check("physical-role-pullup", bool(design.pull("LOCAL_MASTER_N", "+3V3")), design.pull("LOCAL_MASTER_N", "+3V3"))

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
